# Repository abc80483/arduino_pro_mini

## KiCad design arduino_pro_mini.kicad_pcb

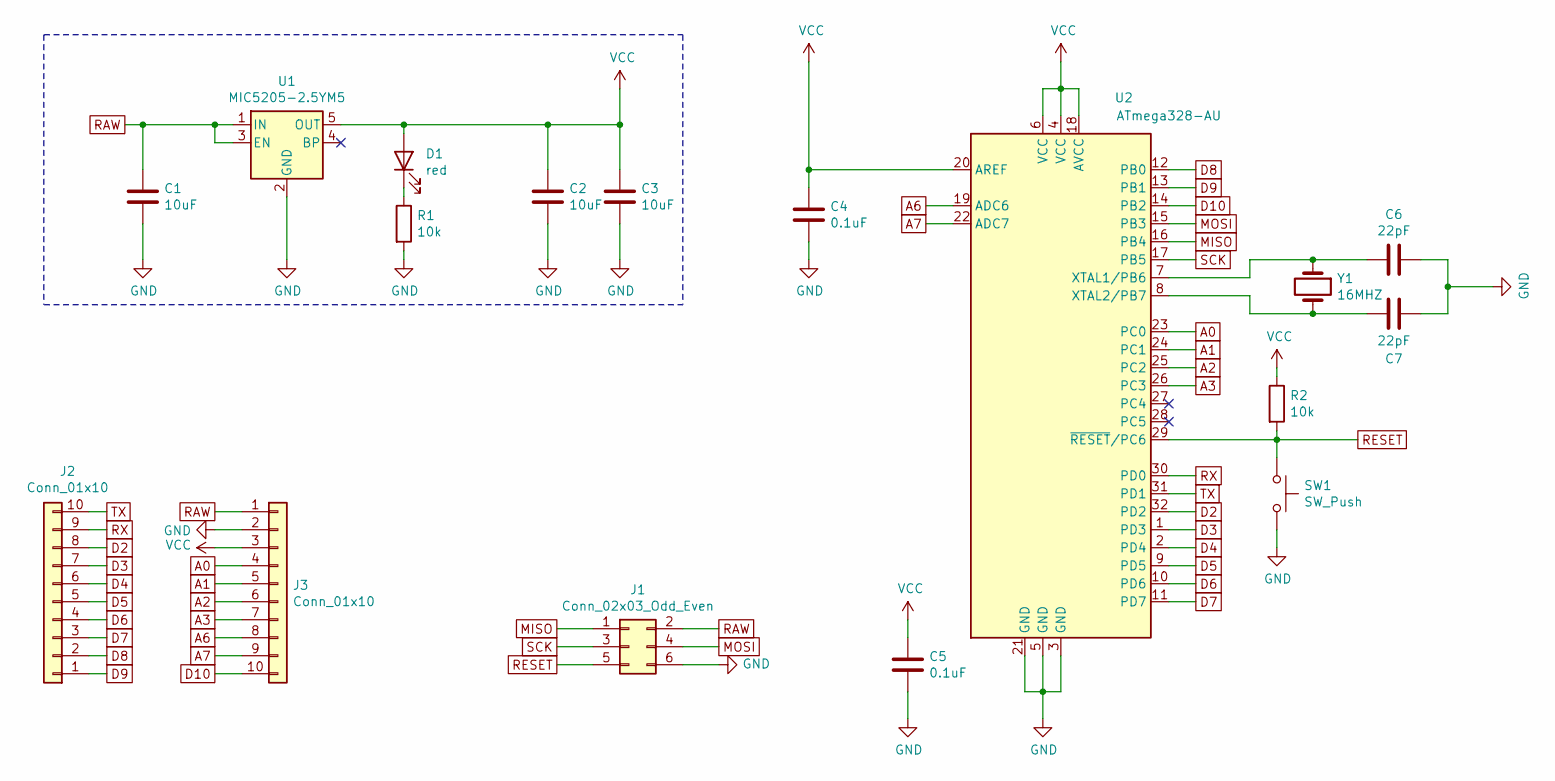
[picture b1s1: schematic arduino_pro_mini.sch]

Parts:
C1, C2, C3: 10uF; C_0603_1608Metric
C4, C5: 0.1uF; C_0603_1608Metric
C6, C7: 22pF; C_0603_1608Metric
D1: red; LED_0603_1608Metric
J1: Conn_02x03_Odd_Even; PinHeader_2x03_P2.54mm_Vertical
J2, J3: Conn_01x10; PinHeader_1x10_P2.54mm_Vertical
R1, R2: 10k; R_0603_1608Metric
SW1: SW_Push; SW_SPST_PTS645
U1: MIC5205-2.5YM5; SOT-23-5
U2: ATmega328-AU; TQFP-32_7x7mm_P0.8mm
Y1: 16MHZ; Crystal_HC49-U_Vertical

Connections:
A0: J3.4, U2.23 (PC0)
A1: J3.5, U2.24 (PC1)
A2: J3.6, U2.25 (PC2)
A3: J3.7, U2.26 (PC3)
A6: J3.8, U2.19 (ADC6)
A7: J3.9, U2.22 (ADC7)
D2: J2.8, U2.32 (PD2)
D3: J2.7, U2.1 (PD3)
D4: J2.6, U2.2 (PD4)
D5: J2.5, U2.9 (PD5)
D6: J2.4, U2.10 (PD6)
D7: J2.3, U2.11 (PD7)
D8: J2.2, U2.12 (PB0)
D9: J2.1, U2.13 (PB1)
D10: J3.10, U2.14 (PB2)
GND: C1.2, C2.2, C3.2, C4.1, C5.1, C6.2, C7.1, J1.6, J3.2, R1.2, SW1.2, U1.2 (GND), U2.3 (GND), U2.5 (GND), U2.21 (GND)
MISO: J1.1, U2.16 (PB4)
MOSI: J1.4, U2.15 (PB3)
unnamed: C6.1, U2.7 (XTAL1/PB6), Y1.1
unnamed: C7.2, U2.8 (XTAL2/PB7), Y1.2
unnamed: D1.1 (K), R1.1
RAW: C1.1, J1.2, J3.1, U1.1 (IN), U1.3 (EN)
RESET: J1.5, R2.2, SW1.1, U2.29 (~RESET~/PC6)
RX: J2.9, U2.30 (PD0)
SCK: J1.3, U2.17 (PB5)
TX: J2.10, U2.31 (PD1)

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
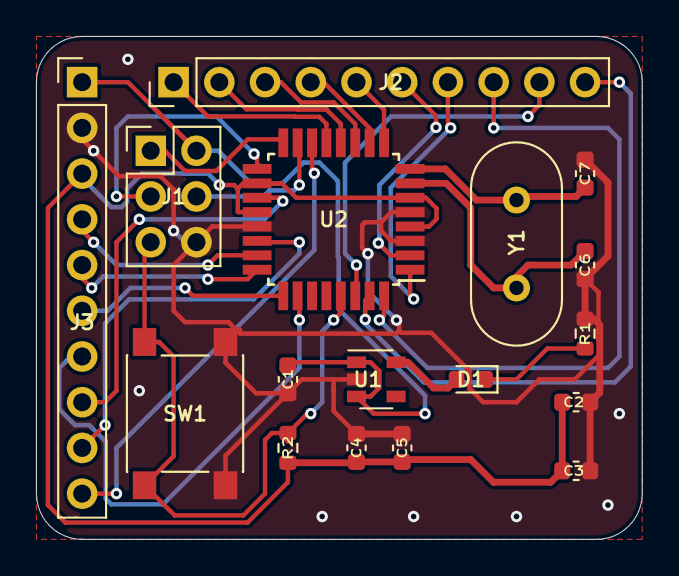
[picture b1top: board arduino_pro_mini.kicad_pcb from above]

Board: 2 copper layers, 33.7 x 27.9 mm, 17 parts (0 on the bottom side), 28 nets.

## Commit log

2021-04-01 complete choose footprint.
2021-04-29 first bgr file upload
2021-04-29 add drl file
2021-04-29 update berger drill file
2021-04-29 pcb autosave nothing change
